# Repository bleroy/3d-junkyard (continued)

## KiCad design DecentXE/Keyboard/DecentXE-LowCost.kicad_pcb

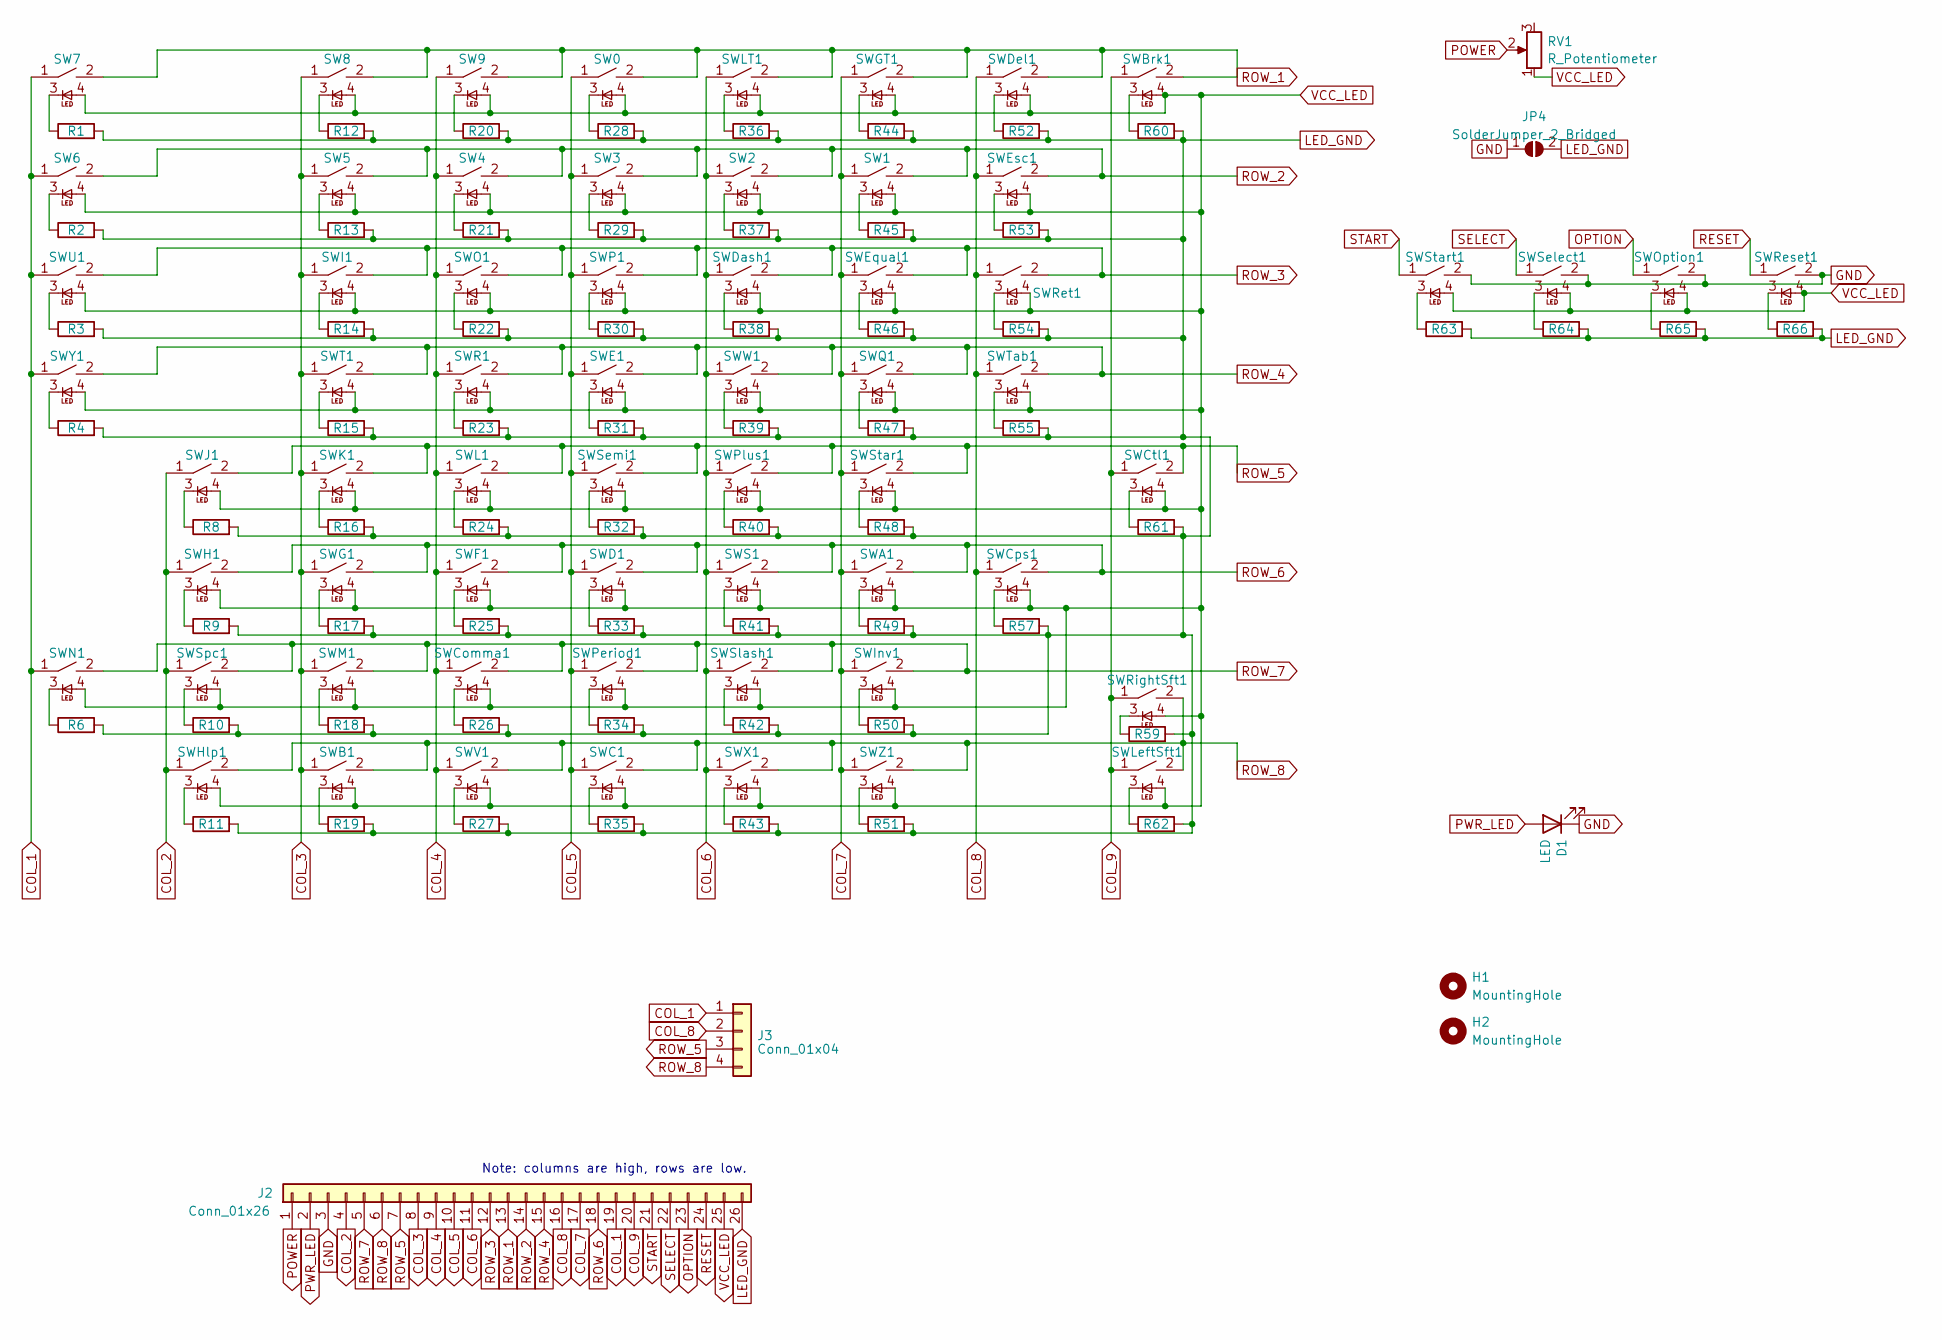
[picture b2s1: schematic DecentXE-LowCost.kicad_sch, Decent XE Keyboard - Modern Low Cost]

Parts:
D1: LED; LED_0603_1608Metric; JLCPCB Part # C2286
H1, H2: MountingHole; MountingHole_3.2mm_M3
J2: Conn_01x26; Molex_200528-0260_1x26-1MP_P1.00mm_Horizontal; JLCPCB Part # C2914085
J3: Conn_01x04; JST_EH_S4B-EH_1x04_P2.50mm_Horizontal
JP4: SolderJumper_2_Bridged; SolderJumper-2_P1.3mm_Bridged_RoundedPad1.0x1.5mm
R1, R2, R3, R4, R6, R8, R9, R10, R11, R12, R13, R14, R15, R16, R17, R18, R19, R20, R21, R22, R23, R24, R25, R26, R27, R28, R29, R30, R31, R32, R33, R34, R35, R36, R37, R38, R39, R40, R41, R42, R43, R44, R45, R46, R47, R48, R49, R50, R51, R52, R53, R54, R55, R57, R59, R60, R61, R62, R63, R64, R65, R66: R; R_0603_1608Metric; JLCPCB Part # C22775
RV1: R_Potentiometer; Potentiometer_Bourns_TC33X_Vertical; JLCPCB Part # C719174
SW0, SW1, SW2, SW3, SW4, SW5, SW6, SW7, SW8, SW9: SW_Push_45deg; MX-1-00U-LED; JLCPCB Part # C193191
SWA1: SW_Push_45deg; MX-1-00U-LED; JLCPCB Part # C193191
SWB1: SW_Push_45deg; MX-1-00U-LED; JLCPCB Part # C193191
SWBrk1: SW_Push_45deg; MX-1-25U-LED; JLCPCB Part # C193191
SWC1: SW_Push_45deg; MX-1-00U-LED; JLCPCB Part # C193191
SWComma1: SW_Push_45deg; MX-1-00U-LED; JLCPCB Part # C193191
SWCps1: SW_Push_45deg; MX-1-75U-LED; JLCPCB Part # C193191
SWCtl1: SW_Push_45deg; MX-1-25U-LED; JLCPCB Part # C193191
SWD1: SW_Push_45deg; MX-1-00U-LED; JLCPCB Part # C193191
SWDash1: SW_Push_45deg; MX-1-00U-LED; JLCPCB Part # C193191
SWDel1: SW_Push_45deg; MX-2-00U-LED; JLCPCB Part # C193191
SWE1: SW_Push_45deg; MX-1-00U-LED; JLCPCB Part # C193191
SWEqual1: SW_Push_45deg; MX-1-00U-LED; JLCPCB Part # C193191
SWEsc1: SW_Push_45deg; MX-1-00U-LED; JLCPCB Part # C193191
SWF1: SW_Push_45deg; MX-1-00U-LED; JLCPCB Part # C193191
SWG1: SW_Push_45deg; MX-1-00U-LED; JLCPCB Part # C193191
SWGT1: SW_Push_45deg; MX-1-00U-LED; JLCPCB Part # C193191
SWH1: SW_Push_45deg; MX-1-00U-LED; JLCPCB Part # C193191
SWHlp1: SW_Push_45deg; Choc-1-50U-Atari-Fn-LED; JLCPCB Part # C193191
SWI1: SW_Push_45deg; MX-1-00U-LED; JLCPCB Part # C193191
SWInv1: SW_Push_45deg; MX-1-00U-LED; JLCPCB Part # C193191
SWJ1: SW_Push_45deg; MX-1-00U-LED; JLCPCB Part # C193191
SWK1: SW_Push_45deg; MX-1-00U-LED; JLCPCB Part # C193191
SWL1: SW_Push_45deg; MX-1-00U-LED; JLCPCB Part # C193191
SWLT1: SW_Push_45deg; MX-1-00U-LED; JLCPCB Part # C193191
SWLeftSft1: SW_Push_45deg; MX-2-25U-LED; JLCPCB Part # C193191
SWM1: SW_Push_45deg; MX-1-00U-LED; JLCPCB Part # C193191
SWN1: SW_Push_45deg; MX-1-00U-LED; JLCPCB Part # C193191
SWO1: SW_Push_45deg; MX-1-00U-LED; JLCPCB Part # C193191
SWOption1: SW_Push_45deg; Choc-1-50U-Atari-Fn-LED; JLCPCB Part # C193191
SWP1: SW_Push_45deg; MX-1-00U-LED; JLCPCB Part # C193191
SWPeriod1: SW_Push_45deg; MX-1-00U-LED; JLCPCB Part # C193191
SWPlus1: SW_Push_45deg; MX-1-00U-LED; JLCPCB Part # C193191
SWQ1: SW_Push_45deg; MX-1-00U-LED; JLCPCB Part # C193191
SWR1: SW_Push_45deg; MX-1-00U-LED; JLCPCB Part # C193191
SWReset1: SW_Push_45deg; Choc-1-50U-Atari-Fn-LED; JLCPCB Part # C193191
SWRet1: SW_Push_45deg; MX-ISO-RETURN; JLCPCB Part # C193191
SWRightSft1: SW_Push_45deg; MX-1-75U-LED; JLCPCB Part # C193191
SWS1: SW_Push_45deg; MX-1-00U-LED; JLCPCB Part # C193191
SWSelect1: SW_Push_45deg; Choc-1-50U-Atari-Fn-LED; JLCPCB Part # C193191
SWSemi1: SW_Push_45deg; MX-1-00U-LED; JLCPCB Part # C193191
SWSlash1: SW_Push_45deg; MX-1-00U-LED; JLCPCB Part # C193191
SWSpc1: SW_Push_45deg; MX-6-25U-LED; JLCPCB Part # C193191
SWStar1: SW_Push_45deg; MX-1-00U-LED; JLCPCB Part # C193191
SWStart1: SW_Push_45deg; Choc-1-50U-Atari-Fn-LED; JLCPCB Part # C193191
SWT1: SW_Push_45deg; MX-1-00U-LED; JLCPCB Part # C193191
SWTab1: SW_Push_45deg; MX-1-50U-LED; JLCPCB Part # C193191
SWU1: SW_Push_45deg; MX-1-00U-LED; JLCPCB Part # C193191
SWV1: SW_Push_45deg; MX-1-00U-LED; JLCPCB Part # C193191
SWW1: SW_Push_45deg; MX-1-00U-LED; JLCPCB Part # C193191
SWX1: SW_Push_45deg; MX-1-00U-LED; JLCPCB Part # C193191
SWY1: SW_Push_45deg; MX-1-00U-LED; JLCPCB Part # C193191
SWZ1: SW_Push_45deg; MX-1-00U-LED; JLCPCB Part # C193191

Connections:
COL_1: J2.19, J3.1, SW6.1, SW7.1, SWN1.1, SWU1.1, SWY1.1
COL_2: J2.4, SWH1.1, SWHlp1.1, SWJ1.1, SWSpc1.1
COL_3: J2.8, SW5.1, SW8.1, SWB1.1, SWG1.1, SWI1.1, SWK1.1, SWM1.1, SWT1.1
COL_4: J2.9, SW4.1, SW9.1, SWComma1.1, SWF1.1, SWL1.1, SWO1.1, SWR1.1, SWV1.1
COL_5: J2.10, SW0.1, SW3.1, SWC1.1, SWD1.1, SWE1.1, SWP1.1, SWPeriod1.1, SWSemi1.1
COL_6: J2.11, SW2.1, SWDash1.1, SWLT1.1, SWPlus1.1, SWS1.1, SWSlash1.1, SWW1.1, SWX1.1
COL_7: J2.17, SW1.1, SWA1.1, SWEqual1.1, SWGT1.1, SWInv1.1, SWQ1.1, SWStar1.1, SWZ1.1
COL_8: J2.16, J3.2, SWCps1.1, SWDel1.1, SWEsc1.1, SWRet1.1, SWTab1.1
COL_9: J2.20, SWBrk1.1, SWCtl1.1, SWLeftSft1.1, SWRightSft1.1
GND: D1.1 (K), J2.3, JP4.1 (A), SWOption1.2, SWReset1.2, SWSelect1.2, SWStart1.2
LED_GND: J2.26, JP4.2 (B), R1.2, R2.2, R3.2, R4.2, R6.2, R8.2, R9.2, R10.2, R11.2, R12.2, R13.2, R14.2, R15.2, R16.2, R17.2, R18.2, R19.2, R20.2, R21.2, R22.2, R23.2, R24.2, R25.2, R26.2, R27.2, R28.2, R29.2, R30.2, R31.2, R32.2, R33.2, R34.2, R35.2, R36.2, R37.2, R38.2, R39.2, R40.2, R41.2, R42.2, R43.2, R44.2, R45.2, R46.2, R47.2, R48.2, R49.2, R50.2, R51.2, R52.2, R53.2, R54.2, R55.2, R57.2, R59.2, R60.2, R61.2, R62.2, R63.2, R64.2, R65.2, R66.2
unnamed: R1.1, SW7.3
unnamed: R2.1, SW6.3
unnamed: R3.1, SWU1.3
unnamed: R4.1, SWY1.3
unnamed: R6.1, SWN1.3
unnamed: R8.1, SWJ1.3
unnamed: R9.1, SWH1.3
unnamed: R10.1, SWSpc1.3
unnamed: R11.1, SWHlp1.3
unnamed: R12.1, SW8.3
unnamed: R13.1, SW5.3
unnamed: R14.1, SWI1.3
unnamed: R15.1, SWT1.3
unnamed: R16.1, SWK1.3
unnamed: R17.1, SWG1.3
unnamed: R18.1, SWM1.3
unnamed: R19.1, SWB1.3
unnamed: R20.1, SW9.3
unnamed: R21.1, SW4.3
unnamed: R22.1, SWO1.3
unnamed: R23.1, SWR1.3
unnamed: R24.1, SWL1.3
unnamed: R25.1, SWF1.3
unnamed: R26.1, SWComma1.3
unnamed: R27.1, SWV1.3
unnamed: R28.1, SW0.3
unnamed: R29.1, SW3.3
unnamed: R30.1, SWP1.3
unnamed: R31.1, SWE1.3
unnamed: R32.1, SWSemi1.3
unnamed: R33.1, SWD1.3
unnamed: R34.1, SWPeriod1.3
unnamed: R35.1, SWC1.3
unnamed: R36.1, SWLT1.3
unnamed: R37.1, SW2.3
unnamed: R38.1, SWDash1.3
unnamed: R39.1, SWW1.3
unnamed: R40.1, SWPlus1.3
unnamed: R41.1, SWS1.3
unnamed: R42.1, SWSlash1.3
unnamed: R43.1, SWX1.3
unnamed: R44.1, SWGT1.3
unnamed: R45.1, SW1.3
unnamed: R46.1, SWEqual1.3
unnamed: R47.1, SWQ1.3
unnamed: R48.1, SWStar1.3
unnamed: R49.1, SWA1.3
unnamed: R50.1, SWInv1.3
unnamed: R51.1, SWZ1.3
unnamed: R52.1, SWDel1.3
unnamed: R53.1, SWEsc1.3
unnamed: R54.1, SWRet1.3
unnamed: R55.1, SWTab1.3
unnamed: R57.1, SWCps1.3
unnamed: R59.1, SWRightSft1.3
unnamed: R60.1, SWBrk1.3
unnamed: R61.1, SWCtl1.3
unnamed: R62.1, SWLeftSft1.3
unnamed: R63.1, SWStart1.3
unnamed: R64.1, SWSelect1.3
unnamed: R65.1, SWOption1.3
unnamed: R66.1, SWReset1.3
OPTION: J2.23, SWOption1.1
POWER: J2.1, RV1.2
PWR_LED: D1.2 (A), J2.2
RESET: J2.24, SWReset1.1
ROW_1: J2.13, SW0.2, SW7.2, SW8.2, SW9.2, SWBrk1.2, SWDel1.2, SWGT1.2, SWLT1.2
ROW_2: J2.14, SW1.2, SW2.2, SW3.2, SW4.2, SW5.2, SW6.2, SWEsc1.2
ROW_3: J2.12, SWDash1.2, SWEqual1.2, SWI1.2, SWO1.2, SWP1.2, SWRet1.2, SWU1.2
ROW_4: J2.15, SWE1.2, SWQ1.2, SWR1.2, SWT1.2, SWTab1.2, SWW1.2, SWY1.2
ROW_5: J2.7, J3.3, SWCtl1.2, SWJ1.2, SWK1.2, SWL1.2, SWPlus1.2, SWSemi1.2, SWStar1.2
ROW_6: J2.18, SWA1.2, SWCps1.2, SWD1.2, SWF1.2, SWG1.2, SWH1.2, SWS1.2
ROW_7: J2.5, SWComma1.2, SWInv1.2, SWM1.2, SWN1.2, SWPeriod1.2, SWSlash1.2, SWSpc1.2
ROW_8: J2.6, J3.4, SWB1.2, SWC1.2, SWHlp1.2, SWLeftSft1.2, SWRightSft1.2, SWV1.2, SWX1.2, SWZ1.2
SELECT: J2.22, SWSelect1.1
START: J2.21, SWStart1.1
VCC_LED: J2.25, RV1.1, SW0.4, SW1.4, SW2.4, SW3.4, SW4.4, SW5.4, SW6.4, SW7.4, SW8.4, SW9.4, SWA1.4, SWB1.4, SWBrk1.4, SWC1.4, SWComma1.4, SWCps1.4, SWCtl1.4, SWD1.4, SWDash1.4, SWDel1.4, SWE1.4, SWEqual1.4, SWEsc1.4, SWF1.4, SWG1.4, SWGT1.4, SWH1.4, SWHlp1.4, SWI1.4, SWInv1.4, SWJ1.4, SWK1.4, SWL1.4, SWLT1.4, SWLeftSft1.4, SWM1.4, SWN1.4, SWO1.4, SWOption1.4, SWP1.4, SWPeriod1.4, SWPlus1.4, SWQ1.4, SWR1.4, SWReset1.4, SWRet1.4, SWRightSft1.4, SWS1.4, SWSelect1.4, SWSemi1.4, SWSlash1.4, SWSpc1.4, SWStar1.4, SWStart1.4, SWT1.4, SWTab1.4, SWU1.4, SWV1.4, SWW1.4, SWX1.4, SWY1.4, SWZ1.4

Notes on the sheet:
Note: columns are high, rows are low.

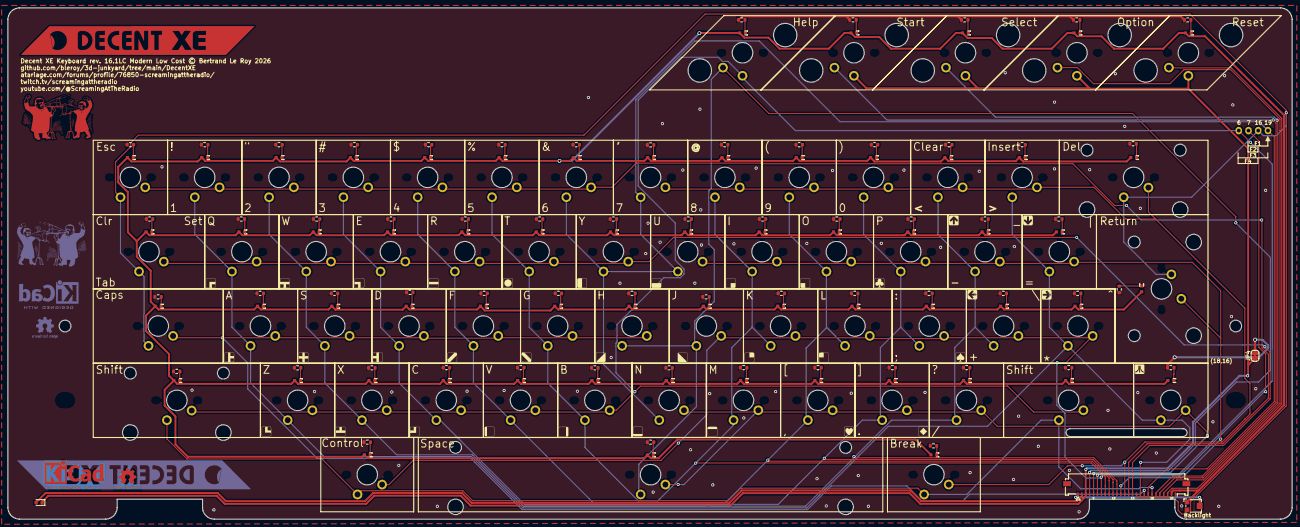
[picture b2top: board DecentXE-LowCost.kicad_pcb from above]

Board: 2 copper layers, 329.2 x 131.1 mm, 133 parts (1 on the bottom side), 88 nets.

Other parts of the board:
H1#2, H1#3: MountingHole; MountingHole_3.2mm_M3

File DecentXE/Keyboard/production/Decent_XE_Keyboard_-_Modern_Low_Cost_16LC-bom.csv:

Designator,Footprint,Quantity,Value,LCSC Part #
D1,0603,1,LED,C2286
J2,Molex_200528-0260_1x26-1MP_P1.00mm_Horizontal,1,Conn_01x26,C2914085
"R1, R10, R11, R12, R13, R14, R15, R16, R17, R18, R19, R2, R20, R21, R22, R23, R24, R25, R26, R27, R28, R29, R3, R30, R31, R32, R33, R34, R35, R36, R37, R38, R39, R4, R40, R41, R42, R43, R44, R45, R46, R47, R48, R49, R50, R51, R52, R53, R54, R55, R57, R59, R6, R60, R61, R62, R63, R64, R65, R66, R8, R9",0603,62,R,C22775
RV1,Potentiometer_Bourns_TC33X_Vertical,1,R_Potentiometer,C719174
"SW0, SW1, SW2, SW3, SW4, SW5, SW6, SW7, SW8, SW9, SWA1, SWB1, SWC1, SWCOMMA1, SWD1, SWDASH1, SWE1, SWEQUAL1, SWESC1, SWF1, SWG1, SWGT1, SWH1, SWI1, SWINV1, SWJ1, SWK1, SWL1, SWLT1, SWM1, SWN1, SWO1, SWP1, SWPERIOD1, SWPLUS1, SWQ1, SWR1, SWS1, SWSEMI1, SWSLASH1, SWSTAR1, SWT1, SWU1, SWV1, SWW1, SWX1, SWY1, SWZ1",MX-1-00U-LED,48,SW_Push_45deg,C193191
"SWBRK1, SWCTL1",MX-1-25U-LED,2,SW_Push_45deg,C193191
"SWCPS1, SWRIGHTSFT1",MX-1-75U-LED,2,SW_Push_45deg,C193191
SWDEL1,MX-2-00U-LED,1,SW_Push_45deg,C193191
"SWHLP1, SWOPTION1, SWRESET1, SWSELECT1, SWSTART1",Choc-1-50U-Atari-Fn-LED,5,SW_Push_45deg,C193191
SWLEFTSFT1,MX-2-25U-LED,1,SW_Push_45deg,C193191
SWRET1,MX-ISO-RETURN,1,SW_Push_45deg,C193191
SWSPC1,MX-6-25U-LED,1,SW_Push_45deg,C193191
SWTAB1,MX-1-50U-LED,1,SW_Push_45deg,C193191

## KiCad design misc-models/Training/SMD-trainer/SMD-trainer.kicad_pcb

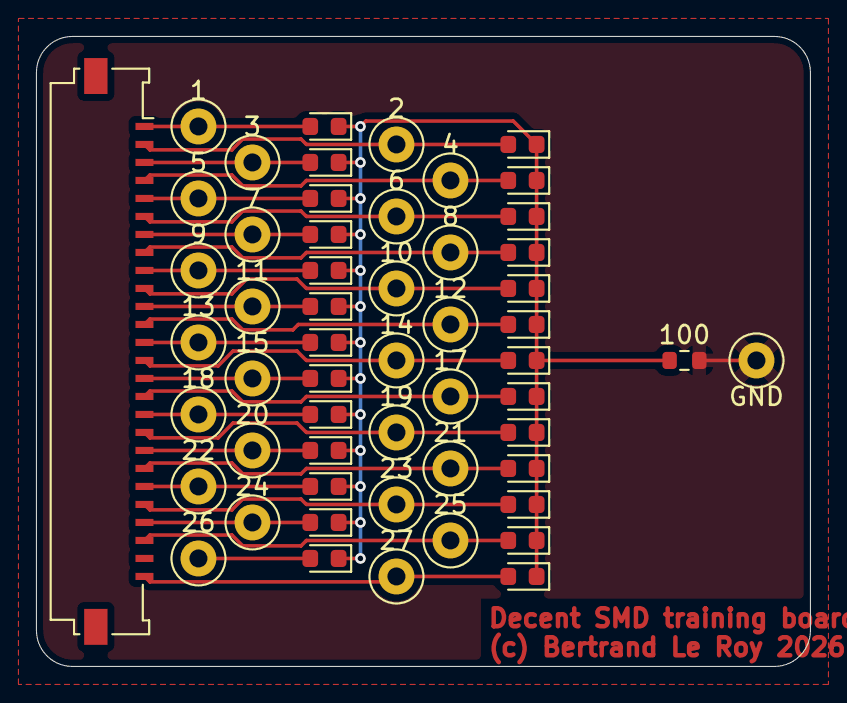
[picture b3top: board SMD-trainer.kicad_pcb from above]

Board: 2 copper layers, 43.0 x 35.0 mm, 55 parts (0 on the bottom side), 28 nets.

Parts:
1, 2, 3, 4, 5, 6, 7, 8, 9, 10, 11, 12, 13, 14, 15, 17, 18, 19, 20, 21, 22, 23, 24, 25, 26, 27: TestPoint; TestPoint_Loop_D2.50mm_Drill1.0mm
100: R; R_0603_1608Metric
D1, D2, D3, D4, D5, D6, D7, D8, D9, D10, D11, D12, D13, D14, D15, D16, D17, D18, D19, D20, D21, D22, D23, D24, D25, D26: LED; LED_0603_1608Metric
GND: TestPoint; TestPoint_Loop_D2.50mm_Drill1.0mm
J1: Conn_01x26_Pin; Molex_200528-0260_1x26-1MP_P1.00mm_Horizontal

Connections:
GND: 100.2, GND.1 (1_1)
unnamed: 27.1 (1_1), D1.2 (A), J1.26
unnamed: 100.1, D1.1 (K), D2.1 (K), D3.1 (K), D4.1 (K), D5.1 (K), D6.1 (K), D7.1 (K), D8.1 (K), D9.1 (K), D10.1 (K), D11.1 (K), D12.1 (K), D13.1 (K), D14.1 (K), D15.1 (K), D16.1 (K), D17.1 (K), D18.1 (K), D19.1 (K), D20.1 (K), D21.1 (K), D22.1 (K), D23.1 (K), D24.1 (K), D25.1 (K), D26.1 (K)
unnamed: 26.1 (1_1), D2.2 (A), J1.25
unnamed: 25.1 (1_1), D3.2 (A), J1.24
unnamed: 24.1 (1_1), D4.2 (A), J1.23
unnamed: 23.1 (1_1), D5.2 (A), J1.22
unnamed: 22.1 (1_1), D6.2 (A), J1.21
unnamed: 21.1 (1_1), D7.2 (A), J1.20
unnamed: 20.1 (1_1), D8.2 (A), J1.19
unnamed: 19.1 (1_1), D9.2 (A), J1.18
unnamed: 18.1 (1_1), D10.2 (A), J1.17
unnamed: 17.1 (1_1), D11.2 (A), J1.16
unnamed: 15.1 (1_1), D12.2 (A), J1.15
unnamed: 14.1 (1_1), D13.2 (A), J1.14
unnamed: 13.1 (1_1), D14.2 (A), J1.13
unnamed: 12.1 (1_1), D15.2 (A), J1.12
unnamed: 11.1 (1_1), D16.2 (A), J1.11
unnamed: 10.1 (1_1), D17.2 (A), J1.10
unnamed: 9.1 (1_1), D18.2 (A), J1.9
unnamed: 8.1 (1_1), D19.2 (A), J1.8
unnamed: 7.1 (1_1), D20.2 (A), J1.7
unnamed: 6.1 (1_1), D21.2 (A), J1.6
unnamed: 5.1 (1_1), D22.2 (A), J1.5
unnamed: 4.1 (1_1), D23.2 (A), J1.4
unnamed: 3.1 (1_1), D24.2 (A), J1.3
unnamed: 2.1 (1_1), D25.2 (A), J1.2
unnamed: 1.1 (1_1), D26.2 (A), J1.1

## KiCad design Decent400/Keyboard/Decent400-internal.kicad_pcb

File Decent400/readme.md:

# Decent 400 mechanical keyboard replacement for Atari 400 computers

If you always wished the Atari 400 had a real keyboard, this is the project for you.

There's been a number of aftermarket keyboards for the Atari 400, but they all faced a big issue: the original membrane "keyboard"'s "keys" are much smaller than standard key caps. There just isn't enough space in the case for a sane layout with full-sized keys. It took a lot of attempts before coming up with the realization that there was an untapped degree of freedom in the design: the spacing of the keys. This is even more true of low-profile key caps, and given how infinitely taller MX switches and caps are compared to the original membrane thing, it made sense to try to build the Decent400 as a low-profile mechanical keyboard. I was finally able in late 2025 to fit the original layout of the computer in its very small space, with modern switches.

There was one final obstacle though, which is that as I'm writing this readme, no company in the world will print custom low-profile key caps. My only option was to somehow find a way to do it myself. When I heard about the [Eufymake](https://www.eufymake.com/) kickstarter for a UV printer capable of transferring a full-color design onto any material, it was clear it could be the last piece to the puzzle. It was a big investment, but I bet on it and waited and waited and waited. Finally, the printer arrived and check this out:

It even has the raised white outline on each key, a very satisfying detail...

The keyboard can be built with your choice of Kailh Choc v1 switches. I prefer the clicky Robins myself, but perfectly good tactile and linear options do exist if that's your preference.

If you're looking to modify an XE computer, head over to [the DecentXE project](../Atari130MX/). For 600XL and 800XL keyboards, go to [the DecentXL project](../DecentXL/). For the 1200XL keyboard, go to [the Decent1200 project](../Decent1200/). For the 800, go to [the Decent800 project](../Decent800/).

## Current version

The current revision of the Decent 400 keyboard is: rev. 5.

## Can I buy one?

The project is open-source, and I encourage everyone to build their own (access to a UV printer can be an obstacle, but you can buy the printed key caps from me). I also sell kits and assembled keyboards for those who are not comfortable with ordering parts, PCBs or using a soldering iron.

How expensive is it? It depends on what you're ordering, but this is a made-to-order custom mechanical keyboard, so not cheap.

## Project history

This is a brand new design that uses a lot of lessons learned from building the [DecentXE](https://github.com/bleroy/3d-junkyard/tree/main/Atari130MX) and the [award-winning DecentXL](https://github.com/bleroy/3d-junkyard/tree/main/DecentXL), but adapts to the specificities of the 400.

## Options

### Switches

Switches are largely a matter of taste. The Decent 400 PCB can be mounted with any Kailh Choc v1 switch.

With any type of switch, there is a wide array of choices. If you're new to the world of mechanical keyboards, there are 3 main families of switch experiences:

* Linear (often red): the switch reacts with mostly constant resistance throughout the course of the key press until it hits the bottom.
* Tactile (often brown): there is a higher resistance at a specific point of the key's course, providing tactile feedback to pressing the key.
* Clicky (often white): an even more pronounced and localized resistance is accompanied with an audible and satisfying click.

My personal preference goes to Choc Robin switches, which are very pleasant clicky switches.

## Design

The Decent 400 project is constituted of the following parts (this is not a BOM but a list of custom parts created for this project; see below for the actual BOM):

* A PCB with adjustable blue backlighting.
* An aluminum or FR4 plate to hold the switches firmly aligned and rigidify the assembly.
* A custom set of Choc v1-compatible modern key caps.
* A connector adapter board
* Cables

## Bill of materials

This project is meant to be reproduced. You'll need a few things that are more or less easy to source, so I've made sure to give multiple roads to success and alternatives for most parts.

It's also an approach that can be easily adapted to other vintage computer keyboards, Atari or not.

### Atari 400 computer

The project is designed around the conservation of the vintage look of the Atari 400 computer and the integration of the keyboard in its original case. As such, you'll need a host 400 computer to receive the end product.

### Key caps

The key caps are the hardest part to source because at the time of writing, nobody's printing custom low-profile caps.

As UV printers are becoming relatively affordable, it has become possible to print blank caps at home.

You'll need a set of blank caps that can be printed in a UV printer.
I'm providing a set of templates and printing support to make it easier to get consistent results.

The space bar key cap is almost impossible to source and must be [printed with black filament](./Caps/SpaceBar-Choc-v1-6U25.3mf).

### Switches

You'll need 63 Choc v1 switches.

### Stabilizers and adapters

The Decent 400 keyboard uses one 2U stabilizers for the left shift key, and one 6.25U stabilizer for the space bar.
Make sure you order the correct low-profile stabilizers.

### PCB

Use [the Gerber](./Keyboard/production/Decent400_keyboard_5.zip), [BOM](./Keyboard/production/bom.csv) and [position](./Keyboard/production/positions.csv) files to order a PCB with all the SMD parts assembled.

The main PCB needs a 2x12 pin male IDC connector.

### Plate

The plate is just a PCB, which can be done in aluminum or FR4. Download [the Gerber](./Plate/production/Decent400_Plate_4.2i.zip) and have it produced in 1.2mm. It is important to check the thickness is 1.2mm and not the default 1.6mm, so that the Choc switches can properly grip it. I recommend having this done in black.

### Connectors

The keyboard connects to the motherboard through a small interface board. A pin header goes into the motherboard connector, and an IDC connector goes to the keyboard. There's also a pair of headers that can be connected to 5V and ground on the 400's power board to provide backlighting.

The connector board needs another 2x12 pin male IDC connector a 22 precision male pin header a a 2 pin angled male header.

You'll need a 24 wire 1.27mm pitch flat cable. 10cm or 15cm is fine since the connector board will be very close to the keyboardś connector.

You'll also need a 22 pin 2.54mm precision male header and a 2 pin 2.54mm pitch angled male header. Finally, two Dupont wires will connect the backlighting to 5V and ground on the Atariś power board.

## Assembly

Once you've gathered all the parts, you can assemble them in the following order:

### Mount the switches onto the plate

Insert switches into the plate with the LED window to the back and the pins to the front.

### Mount the stabilizers

The stabilizers consist of two parts and a rod. They must first be assembled and then added to the plate from the underside.

Thereś plenty of tutorials that get into the details of installing those stabilizers. Here's one:

[Kailh Chox stabilizer installation](https://docs.keeb.io/choc-stabs)

### Get the plate and PCB together

After making sure all the switch pins are vertical and none are bent out of place, carefully align the plate and switches with the PCB. Slowly and carefully complete that assembly, making sure no pins get bent. Once that is done, the plate and PCB should be a few millimeters apart, evenly spaced across the whole surface.

You may secure the boards together with tape or clothespins until you've soldered enough switches.

### Solder the switches onto the PCBs

Solder each switch onto the PCBs.

Note the console key switches are not within the area covered by the plate and need to be soldered separately after being carefully aligned by hand.

### Assemble the connector board

Solder the 24 pin IDC connector to the top of the connector board, the 22 pin header to the bottom and the 2 pin power header to the top.

### Plug the cables

Solder the second 24-pin IDC connector to the bottom of the keyboard and connect both ends of the flat cable into the IDC connectors. 

### Add the key caps

Assemble the key caps onto the switches starting with the stabilized keys. Don't add the caps to the console keys as that will make it difficult to get the keyboard through the tight console key holes.

Your keyboard is now assembled. Let's mount it into the computer.

### Removing the old keyboard

Opening the Atari 400 can be tricky if you haven't done it before. There are some great tutorials and videos showing how to do that. You only need to remove the top of the case, no need to fully disassemble the computer.

Once the top of the case is free, carefully lift it and unplug the keyboard ribbon cable from the connector on the motherboard.

Carefully remove the membrane abomination from the top of the case, taking care not to break the two very small pegs that hold it on the bottom. Some bending will be necessary.

Get the new keyboard in place under the top of the case. Getting the console key switches through is usually the trickiest part. Also take care to get the PCB in place on the bottom.

The top will still be floating, but it will be held by the shielding when we reassemble the computer.

### Connect the LED power lines

The keyboard's backlighting needs to get power from the 400 board since the keyboard connector doesn't have a 5V line. Power and ground taps can be found on the power board.

The black wire is ground and the red one is 5V.

### Connect the keyboard

Carefully insert the pin header on the bottom of the connector board into the motherboard's keyboard connector.

Connect the two power lines to the remaining two pins on the connector board.

### Close the case

Close the case, making sure to hold the keyboard while you're doing it and screw it shut. Now would be a good time to add those console key caps.

Congratulations, you're done! Turn your computer on and enjoy your mechanical keyboard. It's a good idea to go into BASIC and check every key works. There are also [keyboard testers](https://forums.atariage.com/index.php?app=core&module=attach&section=attach&attach_rel_module=post&attach_id=443022) that will allow for a complete check.

## Troubleshooting

Defects and mistakes happen. If when testing your keyboard, you notice a key or a bunch of them don't work, testing and fixing the keyboard is usually quite easy.

The back of the board shows the matrix the keyboard is built on. It's easy, from the indications there to figure out what pins a switch is supposed to connect. It's like coordinates: the keyboard is essentially a matrix of switches with diodes behind them. You can test continuity using the connector pins and the diode testing mode of your multimeter. Connect your multimeter, press the switch. You can also test the switch directly, and test continuity from it to its neighbours and to the connectors. Most problems can be found this way, and if the keyboard needs repairs, it's usually easy to pull an additional wire to fix a damaged trace.

## Acknowledgements

I want to thank [XLFreak](https://forums.atariage.com/profile/63723-xl-freak/) for designing early versions of the modern key cap set for this project.

And of course, many thanks to all those who provided feedback on the [DecentXE keyboard](https://github.com/bleroy/3d-junkyard/tree/main/Atari130MX) over its many revisions or bought a keyboard.

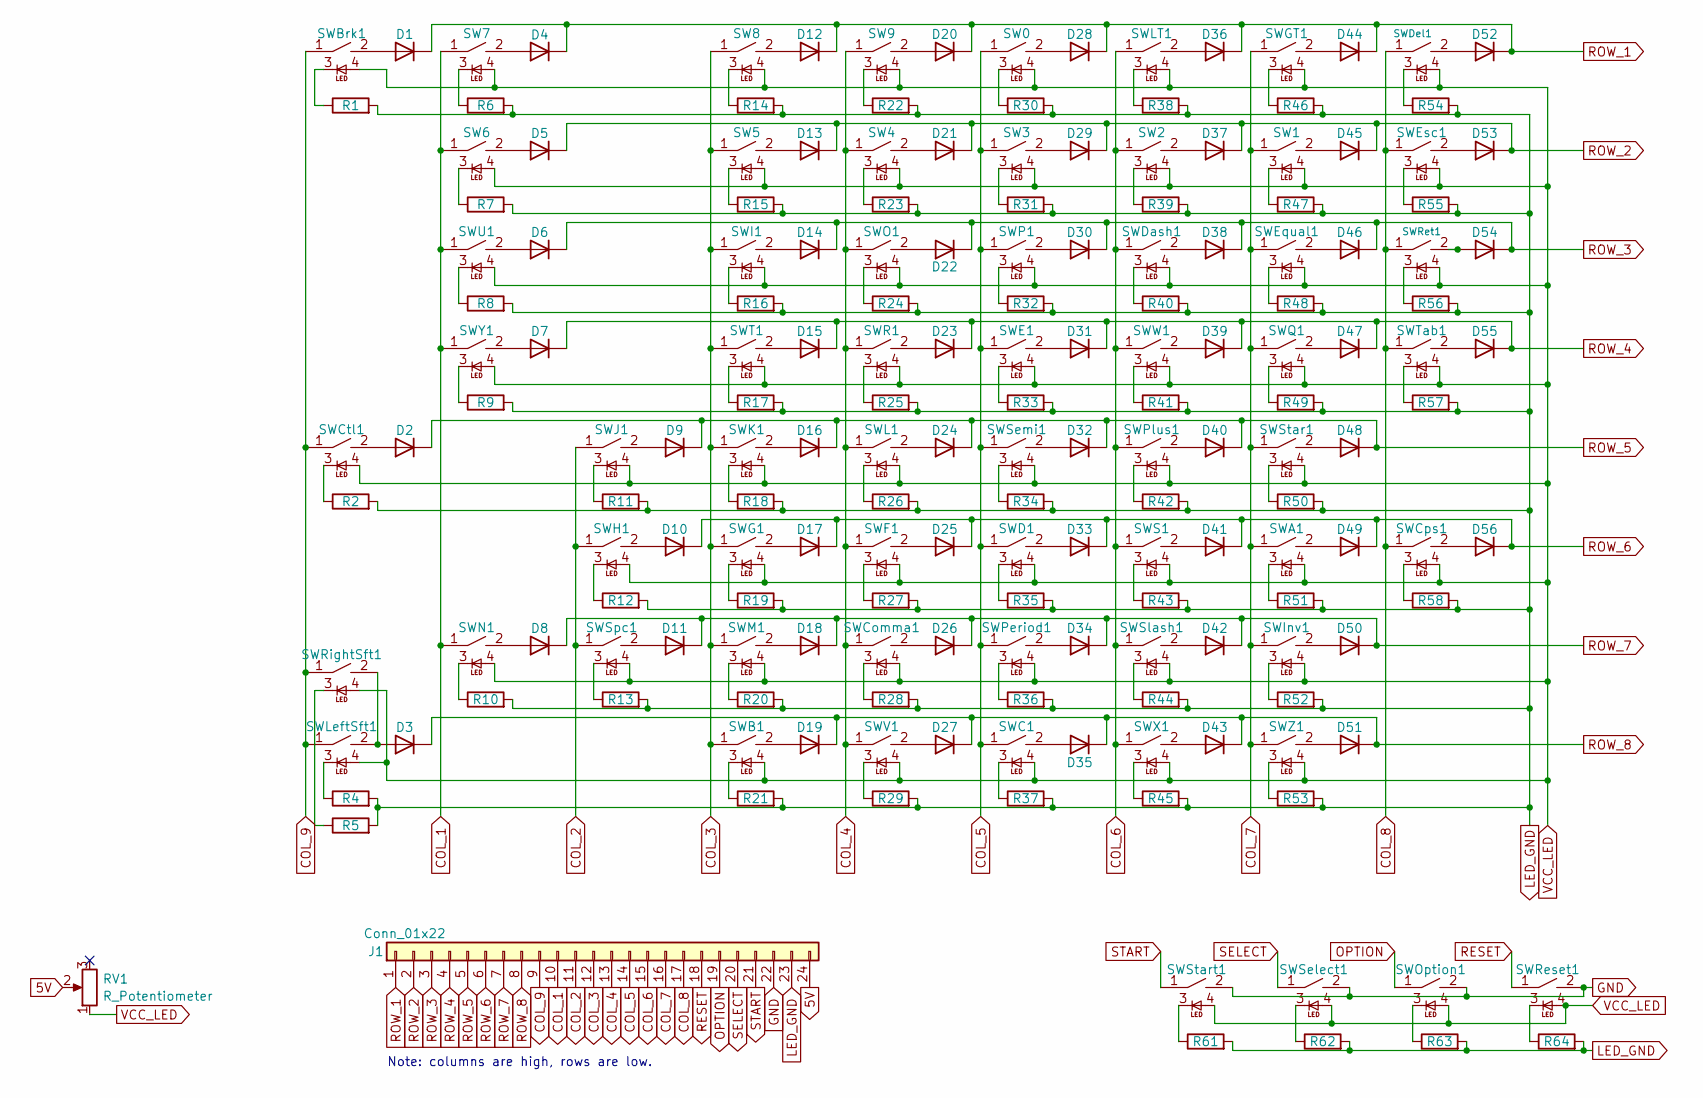
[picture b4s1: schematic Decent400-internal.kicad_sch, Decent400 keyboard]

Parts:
D1, D2, D3, D4, D5, D6, D7, D8, D9, D10, D11, D12, D13, D14, D15, D16, D17, D18, D19, D20, D21, D22, D23, D24, D25, D26, D27, D28, D29, D30, D31, D32, D33, D34, D35, D36, D37, D38, D39, D40, D41, D42, D43, D44, D45, D46, D47, D48, D49, D50, D51, D52, D53, D54, D55, D56: 1N4148W; D_SOD-123; LCSC Part # C81598
J1: Conn_01x22; IDC-Header_2x12_P2.54mm_Vertical
R1, R2, R4, R5, R6, R7, R8, R9, R10, R11, R12, R13, R14, R15, R16, R17, R18, R19, R20, R21, R22, R23, R24, R25, R26, R27, R28, R29, R30, R31, R32, R33, R34, R35, R36, R37, R38, R39, R40, R41, R42, R43, R44, R45, R46, R47, R48, R49, R50, R51, R52, R53, R54, R55, R56, R57, R58, R61, R62, R63, R64: 100; R_0402_1005Metric; LCSC Part # C25076
RV1: R_Potentiometer; Potentiometer_Bourns_TC33X_Vertical; LCSC Part # C720647
SW0, SW1, SW2, SW3, SW4, SW5, SW6, SW7, SW8, SW9: SW_LED; Choc-1-00U-LED; LCSC Part # C2290
SWA1: SW_LED; Choc-1-00U-LED; LCSC Part # C2290
SWB1: SW_LED; Choc-1-00U-LED; LCSC Part # C2290
SWBrk1: SW_LED; Choc-1-00U-LED; LCSC Part # C2290
SWC1: SW_LED; Choc-1-00U-LED; LCSC Part # C2290
SWComma1: SW_LED; Choc-1-00U-LED; LCSC Part # C2290
SWCps1: SW_LED; Choc-1-00U-LED; LCSC Part # C2290
SWCtl1: SW_LED; Choc-1-50U-LED; LCSC Part # C2290
SWD1: SW_LED; Choc-1-00U-LED; LCSC Part # C2290
SWDash1: SW_LED; Choc-1-00U-LED; LCSC Part # C2290
SWDel1: SW_LED; Choc-1-00U-LED; LCSC Part # C2290
SWE1: SW_LED; Choc-1-00U-LED; LCSC Part # C2290
SWEqual1: SW_LED; Choc-1-00U-LED; LCSC Part # C2290
SWEsc1: SW_LED; Choc-1-00U-LED; LCSC Part # C2290
SWF1: SW_LED; Choc-1-00U-LED; LCSC Part # C2290
SWG1: SW_LED; Choc-1-00U-LED; LCSC Part # C2290
SWGT1: SW_LED; Choc-1-00U-LED; LCSC Part # C2290
SWH1: SW_LED; Choc-1-00U-LED; LCSC Part # C2290
SWI1: SW_LED; Choc-1-00U-LED; LCSC Part # C2290
SWInv1: SW_LED; Choc-1-00U-LED; LCSC Part # C2290
SWJ1: SW_LED; Choc-1-00U-LED; LCSC Part # C2290
SWK1: SW_LED; Choc-1-00U-LED; LCSC Part # C2290
SWL1: SW_LED; Choc-1-00U-LED; LCSC Part # C2290
SWLT1: SW_LED; Choc-1-00U-LED; LCSC Part # C2290
SWLeftSft1: SW_LED; Choc-2-00U-LED; LCSC Part # C2290
SWM1: SW_LED; Choc-1-00U-LED; LCSC Part # C2290
SWN1: SW_LED; Choc-1-00U-LED; LCSC Part # C2290
SWO1: SW_LED; Choc-1-00U-LED; LCSC Part # C2290
SWOption1: SW_LED; Choc-1-00U-LED; LCSC Part # C2290
SWP1: SW_LED; Choc-1-00U-LED; LCSC Part # C2290
SWPeriod1: SW_LED; Choc-1-00U-LED; LCSC Part # C2290
SWPlus1: SW_LED; Choc-1-00U-LED; LCSC Part # C2290
SWQ1: SW_LED; Choc-1-00U-LED; LCSC Part # C2290
SWR1: SW_LED; Choc-1-00U-LED; LCSC Part # C2290
SWReset1: SW_LED; Choc-1-00U-LED; LCSC Part # C2290
SWRet1: SW_LED; Choc-1-25U-LED; LCSC Part # C2290
SWRightSft1: SW_LED; Choc-1-25U-LED; LCSC Part # C2290
SWS1: SW_LED; Choc-1-00U-LED; LCSC Part # C2290
SWSelect1: SW_LED; Choc-1-00U-LED; LCSC Part # C2290
SWSemi1: SW_LED; Choc-1-00U-LED; LCSC Part # C2290
SWSlash1: SW_LED; Choc-1-00U-LED; LCSC Part # C2290
SWSpc1: SW_LED; Choc-6-25U-LED; LCSC Part # C2290
SWStar1: SW_LED; Choc-1-00U-LED; LCSC Part # C2290
SWStart1: SW_LED; Choc-1-00U-LED; LCSC Part # C2290
SWT1: SW_LED; Choc-1-00U-LED; LCSC Part # C2290
SWTab1: SW_LED; Choc-1-50U-LED; LCSC Part # C2290
SWU1: SW_LED; Choc-1-00U-LED; LCSC Part # C2290
SWV1: SW_LED; Choc-1-00U-LED; LCSC Part # C2290
SWW1: SW_LED; Choc-1-00U-LED; LCSC Part # C2290
SWX1: SW_LED; Choc-1-00U-LED; LCSC Part # C2290
SWY1: SW_LED; Choc-1-00U-LED; LCSC Part # C2290
SWZ1: SW_LED; Choc-1-00U-LED; LCSC Part # C2290

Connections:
5V: J1.24, RV1.2
COL_1: J1.10, SW6.1, SW7.1, SWN1.1, SWU1.1, SWY1.1
COL_2: J1.11, SWH1.1, SWJ1.1, SWSpc1.1
COL_3: J1.12, SW5.1, SW8.1, SWB1.1, SWG1.1, SWI1.1, SWK1.1, SWM1.1, SWT1.1
COL_4: J1.13, SW4.1, SW9.1, SWComma1.1, SWF1.1, SWL1.1, SWO1.1, SWR1.1, SWV1.1
COL_5: J1.14, SW0.1, SW3.1, SWC1.1, SWD1.1, SWE1.1, SWP1.1, SWPeriod1.1, SWSemi1.1
COL_6: J1.15, SW2.1, SWDash1.1, SWLT1.1, SWPlus1.1, SWS1.1, SWSlash1.1, SWW1.1, SWX1.1
COL_7: J1.16, SW1.1, SWA1.1, SWEqual1.1, SWGT1.1, SWInv1.1, SWQ1.1, SWStar1.1, SWZ1.1
COL_8: J1.17, SWCps1.1, SWDel1.1, SWEsc1.1, SWRet1.1, SWTab1.1
COL_9: J1.9, SWBrk1.1, SWCtl1.1, SWLeftSft1.1, SWRightSft1.1
GND: J1.22, SWOption1.2, SWReset1.2, SWSelect1.2, SWStart1.2
LED_GND: J1.23, R1.2, R2.2, R4.2, R5.2, R6.2, R7.2, R8.2, R9.2, R10.2, R11.2, R12.2, R13.2, R14.2, R15.2, R16.2, R17.2, R18.2, R19.2, R20.2, R21.2, R22.2, R23.2, R24.2, R25.2, R26.2, R27.2, R28.2, R29.2, R30.2, R31.2, R32.2, R33.2, R34.2, R35.2, R36.2, R37.2, R38.2, R39.2, R40.2, R41.2, R42.2, R43.2, R44.2, R45.2, R46.2, R47.2, R48.2, R49.2, R50.2, R51.2, R52.2, R53.2, R54.2, R55.2, R56.2, R57.2, R58.2, R61.2, R62.2, R63.2, R64.2
unnamed: D1.2 (A), SWBrk1.2
unnamed: D2.2 (A), SWCtl1.2
unnamed: D3.2 (A), SWLeftSft1.2, SWRightSft1.2
unnamed: D4.2 (A), SW7.2
unnamed: D5.2 (A), SW6.2
unnamed: D6.2 (A), SWU1.2
unnamed: D7.2 (A), SWY1.2
unnamed: D8.2 (A), SWN1.2
unnamed: D9.2 (A), SWJ1.2
unnamed: D10.2 (A), SWH1.2
unnamed: D11.2 (A), SWSpc1.2
unnamed: D12.2 (A), SW8.2
unnamed: D13.2 (A), SW5.2
unnamed: D14.2 (A), SWI1.2
unnamed: D15.2 (A), SWT1.2
unnamed: D16.2 (A), SWK1.2
unnamed: D17.2 (A), SWG1.2
unnamed: D18.2 (A), SWM1.2
unnamed: D19.2 (A), SWB1.2
unnamed: D20.2 (A), SW9.2
unnamed: D21.2 (A), SW4.2
unnamed: D22.2 (A), SWO1.2
unnamed: D23.2 (A), SWR1.2
unnamed: D24.2 (A), SWL1.2
unnamed: D25.2 (A), SWF1.2
unnamed: D26.2 (A), SWComma1.2
unnamed: D27.2 (A), SWV1.2
unnamed: D28.2 (A), SW0.2
unnamed: D29.2 (A), SW3.2
unnamed: D30.2 (A), SWP1.2
unnamed: D31.2 (A), SWE1.2
unnamed: D32.2 (A), SWSemi1.2
unnamed: D33.2 (A), SWD1.2
unnamed: D34.2 (A), SWPeriod1.2
unnamed: D35.2 (A), SWC1.2
unnamed: D36.2 (A), SWLT1.2
unnamed: D37.2 (A), SW2.2
unnamed: D38.2 (A), SWDash1.2
unnamed: D39.2 (A), SWW1.2
unnamed: D40.2 (A), SWPlus1.2
unnamed: D41.2 (A), SWS1.2
unnamed: D42.2 (A), SWSlash1.2
unnamed: D43.2 (A), SWX1.2
unnamed: D44.2 (A), SWGT1.2
unnamed: D45.2 (A), SW1.2
unnamed: D46.2 (A), SWEqual1.2
unnamed: D47.2 (A), SWQ1.2
unnamed: D48.2 (A), SWStar1.2
unnamed: D49.2 (A), SWA1.2
unnamed: D50.2 (A), SWInv1.2
unnamed: D51.2 (A), SWZ1.2
unnamed: D52.2 (A), SWDel1.2
unnamed: D53.2 (A), SWEsc1.2
unnamed: D54.2 (A), SWRet1.2
unnamed: D55.2 (A), SWTab1.2
unnamed: D56.2 (A), SWCps1.2
unnamed: R1.1, SWBrk1.3
unnamed: R2.1, SWCtl1.3
unnamed: R4.1, SWLeftSft1.3
unnamed: R5.1, SWRightSft1.3
unnamed: R6.1, SW7.3
unnamed: R7.1, SW6.3
unnamed: R8.1, SWU1.3
unnamed: R9.1, SWY1.3
unnamed: R10.1, SWN1.3
unnamed: R11.1, SWJ1.3
unnamed: R12.1, SWH1.3
unnamed: R13.1, SWSpc1.3
unnamed: R14.1, SW8.3
unnamed: R15.1, SW5.3
unnamed: R16.1, SWI1.3
unnamed: R17.1, SWT1.3
unnamed: R18.1, SWK1.3
unnamed: R19.1, SWG1.3
unnamed: R20.1, SWM1.3
unnamed: R21.1, SWB1.3
unnamed: R22.1, SW9.3
unnamed: R23.1, SW4.3
unnamed: R24.1, SWO1.3
unnamed: R25.1, SWR1.3
unnamed: R26.1, SWL1.3
unnamed: R27.1, SWF1.3
unnamed: R28.1, SWComma1.3
unnamed: R29.1, SWV1.3
unnamed: R30.1, SW0.3
unnamed: R31.1, SW3.3
unnamed: R32.1, SWP1.3
unnamed: R33.1, SWE1.3
unnamed: R34.1, SWSemi1.3
unnamed: R35.1, SWD1.3
unnamed: R36.1, SWPeriod1.3
unnamed: R37.1, SWC1.3
unnamed: R38.1, SWLT1.3
unnamed: R39.1, SW2.3
unnamed: R40.1, SWDash1.3
unnamed: R41.1, SWW1.3
unnamed: R42.1, SWPlus1.3
unnamed: R43.1, SWS1.3
unnamed: R44.1, SWSlash1.3
unnamed: R45.1, SWX1.3
unnamed: R46.1, SWGT1.3
unnamed: R47.1, SW1.3
unnamed: R48.1, SWEqual1.3
unnamed: R49.1, SWQ1.3
unnamed: R50.1, SWStar1.3
unnamed: R51.1, SWA1.3
unnamed: R52.1, SWInv1.3
unnamed: R53.1, SWZ1.3
unnamed: R54.1, SWDel1.3
unnamed: R55.1, SWEsc1.3
unnamed: R56.1, SWRet1.3
unnamed: R57.1, SWTab1.3
unnamed: R58.1, SWCps1.3
unnamed: R61.1, SWStart1.3
unnamed: R62.1, SWSelect1.3
unnamed: R63.1, SWOption1.3
unnamed: R64.1, SWReset1.3
OPTION: J1.19, SWOption1.1
RESET: J1.18, SWReset1.1
ROW_1: D1.1 (K), D4.1 (K), D12.1 (K), D20.1 (K), D28.1 (K), D36.1 (K), D44.1 (K), D52.1 (K), J1.1
ROW_2: D5.1 (K), D13.1 (K), D21.1 (K), D29.1 (K), D37.1 (K), D45.1 (K), D53.1 (K), J1.2
ROW_3: D6.1 (K), D14.1 (K), D22.1 (K), D30.1 (K), D38.1 (K), D46.1 (K), D54.1 (K), J1.3
ROW_4: D7.1 (K), D15.1 (K), D23.1 (K), D31.1 (K), D39.1 (K), D47.1 (K), D55.1 (K), J1.4
ROW_5: D2.1 (K), D9.1 (K), D16.1 (K), D24.1 (K), D32.1 (K), D40.1 (K), D48.1 (K), J1.5
ROW_6: D10.1 (K), D17.1 (K), D25.1 (K), D33.1 (K), D41.1 (K), D49.1 (K), D56.1 (K), J1.6
ROW_7: D8.1 (K), D11.1 (K), D18.1 (K), D26.1 (K), D34.1 (K), D42.1 (K), D50.1 (K), J1.7
ROW_8: D3.1 (K), D19.1 (K), D27.1 (K), D35.1 (K), D43.1 (K), D51.1 (K), J1.8
SELECT: J1.20, SWSelect1.1
START: J1.21, SWStart1.1
VCC_LED: RV1.1, SW0.4, SW1.4, SW2.4, SW3.4, SW4.4, SW5.4, SW6.4, SW7.4, SW8.4, SW9.4, SWA1.4, SWB1.4, SWBrk1.4, SWC1.4, SWComma1.4, SWCps1.4, SWCtl1.4, SWD1.4, SWDash1.4, SWDel1.4, SWE1.4, SWEqual1.4, SWEsc1.4, SWF1.4, SWG1.4, SWGT1.4, SWH1.4, SWI1.4, SWInv1.4, SWJ1.4, SWK1.4, SWL1.4, SWLT1.4, SWLeftSft1.4, SWM1.4, SWN1.4, SWO1.4, SWOption1.4, SWP1.4, SWPeriod1.4, SWPlus1.4, SWQ1.4, SWR1.4, SWReset1.4, SWRet1.4, SWRightSft1.4, SWS1.4, SWSelect1.4, SWSemi1.4, SWSlash1.4, SWSpc1.4, SWStar1.4, SWStart1.4, SWT1.4, SWTab1.4, SWU1.4, SWV1.4, SWW1.4, SWX1.4, SWY1.4, SWZ1.4

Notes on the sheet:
Note: columns are high, rows are low.
